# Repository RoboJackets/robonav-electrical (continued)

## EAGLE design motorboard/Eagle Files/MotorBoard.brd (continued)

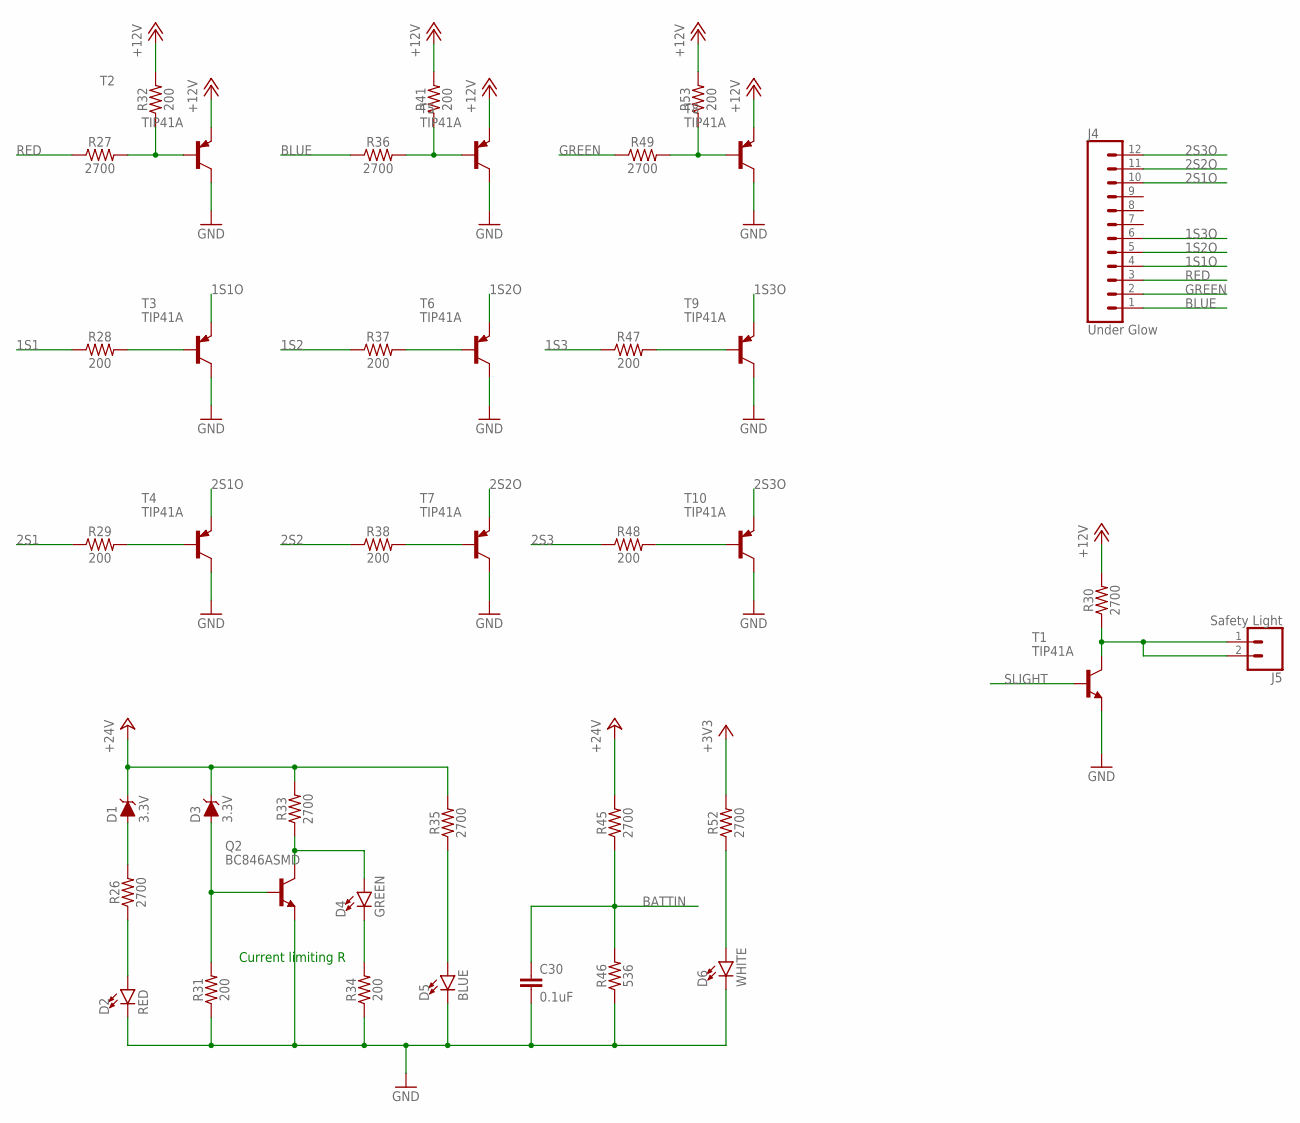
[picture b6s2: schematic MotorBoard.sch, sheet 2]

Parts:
C30: 0.1uF; 0603
D1, D3: 3.3V; SOD-323
D2: RED; LED-0603
D4: GREEN; LED-0603
D5: BLUE; LED-0603
D6: WHITE; LED-0603
J4: Under Glow; 1X12_LOCK_LONGPADS
J5: Safety Light; MOLEX-1X2
Q2: BC846ASMD; SOT23
R26, R27, R30, R33, R35, R36, R45, R49, R52: 2700; 0603
R28, R29, R31, R32, R34, R37, R38, R41, R47, R48, R53: 200; 0603
R46: 536; 0603
T1, T2, T3, T4, T5, T6, T7, T8, T9, T10: TIP41A; TO220V

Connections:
1S1: R28.1; also elsewhere on the board
1S1O: J4.4, T3.3 (E)
1S2: R37.1; also elsewhere on the board
1S2O: J4.5, T6.3 (E)
1S3: R47.1; also elsewhere on the board
1S3O: J4.6, T9.3 (E)
2S1: R29.1; also elsewhere on the board
2S1O: J4.10, T4.3 (E)
2S2: R38.1; also elsewhere on the board
2S2O: J4.11, T7.3 (E)
2S3: R48.1; also elsewhere on the board
2S3O: J4.12, T10.3 (E)
+3V3: R52.2; also elsewhere on the board
+12V: R30.2, R32.2, R41.2, R53.2, T2.3 (E), T5.3 (E), T8.3 (E); also elsewhere on the board
+24V: D1.C, D3.C, R33.2, R35.2, R45.2; also elsewhere on the board
BATTIN: C30.1, R45.1, R46.2; also elsewhere on the board
BLUE: J4.1, R36.1
GND: C30.2, D2.C, D5.C, D6.C, Q2.2 (E), R31.1, R34.1, R46.1, T1.3 (E), T2.2 (C), T3.2 (C), T4.2 (C), T5.2 (C), T6.2 (C), T7.2 (C), T8.2 (C), T9.2 (C), T10.2 (C); also elsewhere on the board
GREEN: J4.2, R49.1
unnamed: J5.1, J5.2, R30.1, T1.2 (C)
unnamed: R27.2, R32.1, T2.1 (B)
unnamed: R36.2, R41.1, T5.1 (B)
unnamed: R49.2, R53.1, T8.1 (B)
unnamed: R47.2, T9.1 (B)
unnamed: R37.2, T6.1 (B)
unnamed: R28.2, T3.1 (B)
unnamed: R29.2, T4.1 (B)
unnamed: R38.2, T7.1 (B)
unnamed: R48.2, T10.1 (B)
unnamed: D1.A, R26.2
unnamed: D2.A, R26.1
unnamed: D4.C, R34.2
unnamed: D3.A, Q2.1 (B), R31.2
unnamed: D5.A, R35.1
unnamed: D4.A, Q2.3 (C), R33.1
unnamed: D6.A, R52.1
RED: J4.3, R27.1
SLIGHT: T1.1 (B); also elsewhere on the board

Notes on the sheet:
Current limiting R

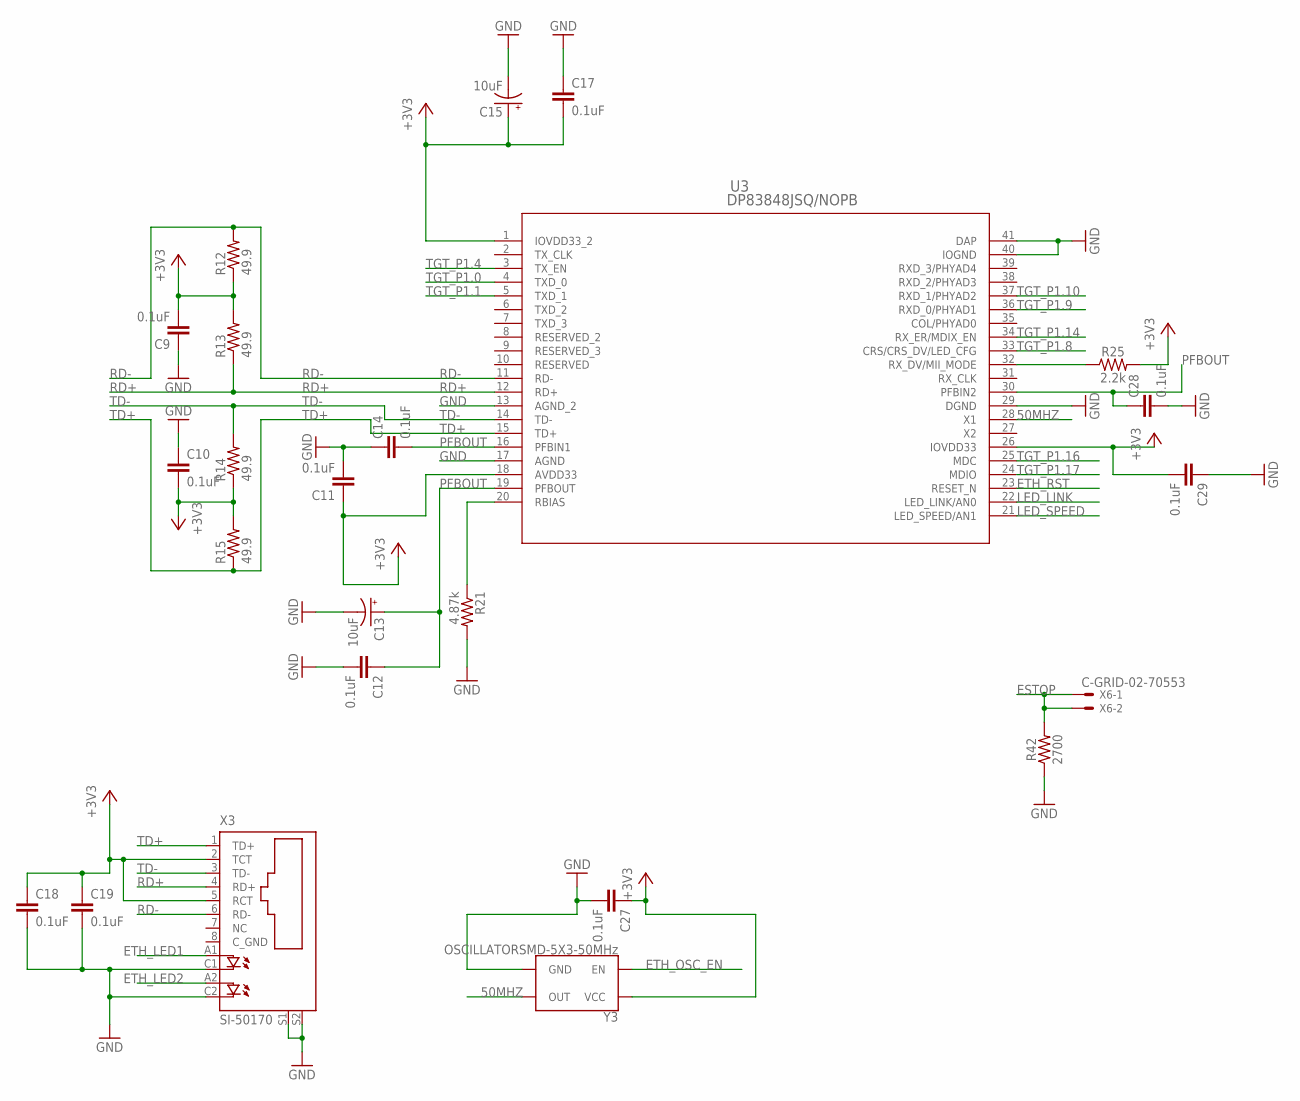
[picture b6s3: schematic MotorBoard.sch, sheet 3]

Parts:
C9, C10, C11, C12, C14, C17, C18, C19, C27, C28, C29: 0.1uF; 0603
C13, C15: 10uF; 0603-POLAR
R12, R13, R14, R15: 49.9; R0603
R21: 4.87k; R0603
R25: 2.2k; 0603
R42: 2700; 0603
U3: DP83848JSQ/NOPB; SQA40B
X3: SI-50170
X6: C-GRID-02-70553; 70553-02
Y3: OSCILLATORSMD-5X3-50MHz; OSCILLATOR-SMD-5X3.2

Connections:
50MHZ: U3.28 (X1), Y3.3 (OUT); also elsewhere on the board
+3V3: C9.2, C10.2, C11.1, C15.+, C17.2, C18.1, C19.1, C27.1, C29.2, R12.1, R13.2, R14.1, R15.2, R25.2, U3.1 (IOVDD33_2), U3.18 (AVDD33), U3.26 (IOVDD33), X3.2 (TCT), X3.5 (RCT), Y3.4 (VCC); also elsewhere on the board
ESTOP: R42.2, X6.1, X6.2; also elsewhere on the board
ETH_LED1: X3.A1 (A); also elsewhere on the board
ETH_LED2: X3.A2 (A1); also elsewhere on the board
ETH_OSC_EN: Y3.1 (EN); also elsewhere on the board
ETH_RST: U3.23 (RESET_N); also elsewhere on the board
GND: C9.1, C10.1, C11.2, C12.2, C13.-, C14.1, C15.-, C17.1, C18.2, C19.2, C27.2, C28.2, C29.1, R21.2, R42.1, U3.13 (AGND_2), U3.17 (AGND), U3.29 (DGND), U3.40 (IOGND), U3.41 (DAP), X3.C1 (C), X3.C2 (C1), X3.S1, X3.S2, Y3.2 (GND); also elsewhere on the board
LED_LINK: U3.22 (LED_LINK/AN0); also elsewhere on the board
LED_SPEED: U3.21 (LED_SPEED/AN1); also elsewhere on the board
unnamed: R21.1, U3.20 (RBIAS)
unnamed: R25.1, U3.32 (RX_DV/MII_MODE)
PFBOUT: C12.1, C13.+, C14.2, C28.1, U3.16 (PFBIN1), U3.19 (PFBOUT), U3.30 (PFBIN2)
RD+: R13.1, U3.12 (RD+), X3.4 (RD+)
RD-: R12.2, U3.11 (RD-), X3.6 (RD-)
TD+: R15.1, U3.15 (TD+), X3.1 (TD+)
TD-: R14.2, U3.14 (TD-), X3.3 (TD-)
TGT_P1.0: U3.4 (TXD_0); also elsewhere on the board
TGT_P1.1: U3.5 (TXD_1); also elsewhere on the board
TGT_P1.4: U3.3 (TX_EN); also elsewhere on the board
TGT_P1.8: U3.33 (CRS/CRS_DV/LED_CFG); also elsewhere on the board
TGT_P1.9: U3.36 (RXD_0/PHYAD1); also elsewhere on the board
TGT_P1.10: U3.37 (RXD_1/PHYAD2); also elsewhere on the board
TGT_P1.14: U3.34 (RX_ER/MDIX_EN); also elsewhere on the board
TGT_P1.16: U3.25 (MDC); also elsewhere on the board
TGT_P1.17: U3.24 (MDIO); also elsewhere on the board

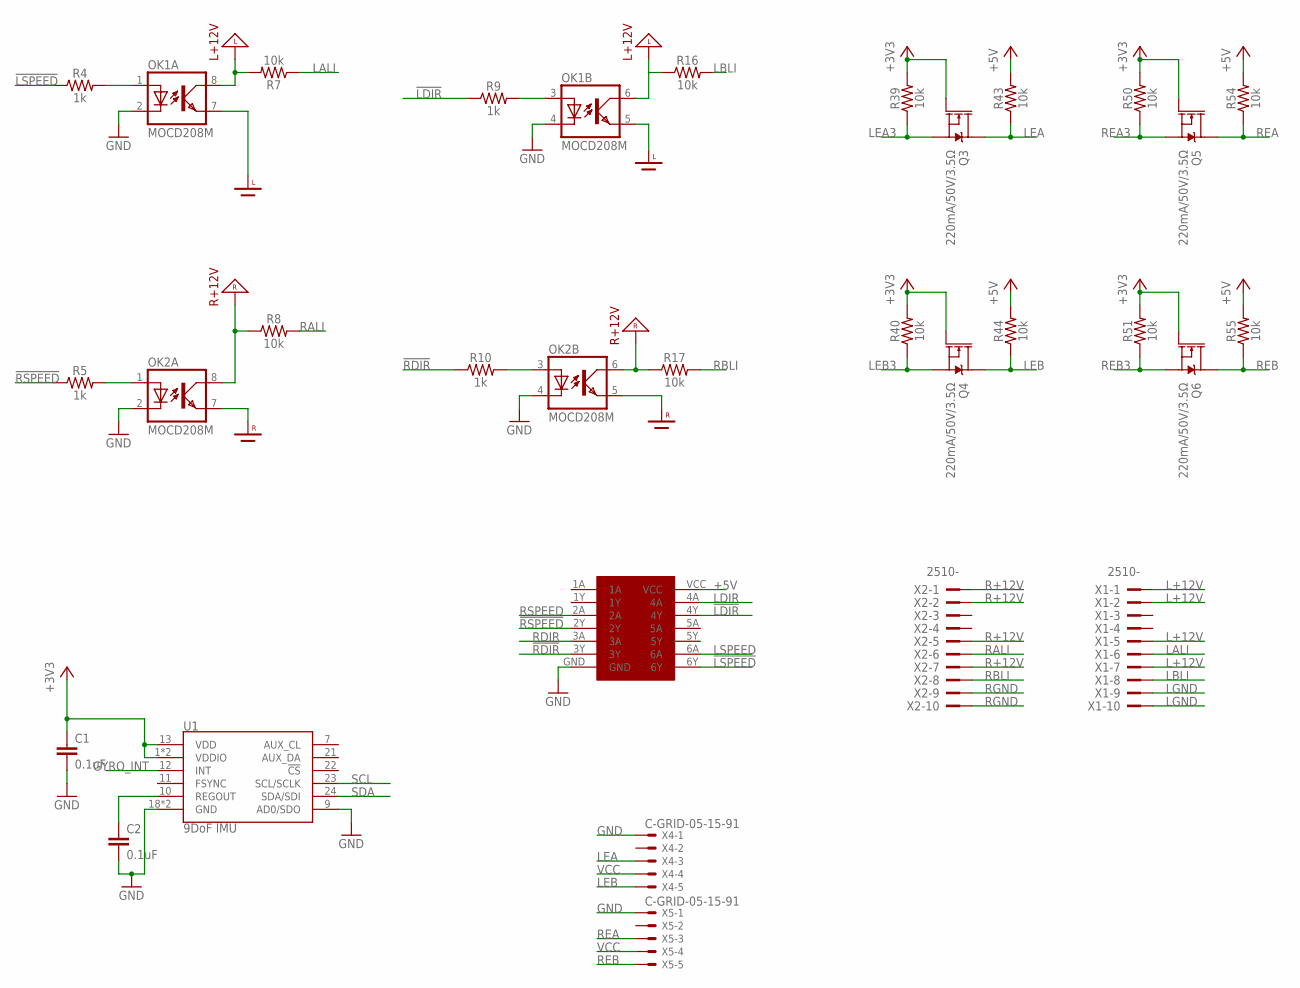
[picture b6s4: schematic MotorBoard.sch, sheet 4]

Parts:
C1, C2: 0.1uF; 0603
OK1, OK2: MOCD208M; SOIC08-FAIRCHILD
Q3, Q4, Q5, Q6: 220mA/50V/3.5Ω; SOT23-3
R4, R5, R9, R10: 1k; 0603
R7, R8, R16, R17, R39, R40, R43, R44, R50, R51, R54, R55: 10k; 0603
U1: 9DoF IMU; QFN24-3X3
U$14: ICHEXINV; 74HC14
X1, X2: 2510-; PAK100/2500-10
X4, X5: C-GRID-05-15-91; 15-91-05

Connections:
!LDIR!: R9.1, U$14.4Y
!LSPEED!: R4.1, U$14.6Y
!RDIR!: R10.1, U$14.3Y
!RSPEED!: R5.1, U$14.2Y
+3V3: C1.1, Q3.1 (G), Q4.1 (G), Q5.1 (G), Q6.1 (G), R39.2, R40.2, R50.2, R51.2, U1.1 (VDDIO), U1.8 (VDDIO), U1.13 (VDD); also elsewhere on the board
+5V: R43.2, R44.2, R54.2, R55.2, U$14.VCC; also elsewhere on the board
GND: C1.2, C2.2, OK1.2 (C), OK1.4 (C), OK2.2 (C), OK2.4 (C), U1.9 (AD0/SDO), U1.18 (GND), U1.20 (GND), U$14.GND, X4.1, X5.1; also elsewhere on the board
GYRO_INT: U1.12 (INT); also elsewhere on the board
L+12V: OK1.6 (COL), OK1.8 (COL), R7.2, R16.1, X1.1, X1.2, X1.5, X1.7
LALI: R7.1, X1.6
LBLI: R16.2, X1.8
LDIR: U$14.4A; also elsewhere on the board
LEA: Q3.3 (D), R43.1, X4.3
LEA3: Q3.2 (S), R39.1; also elsewhere on the board
LEB: Q4.3 (D), R44.1, X4.5
LEB3: Q4.2 (S), R40.1; also elsewhere on the board
LGND: OK1.5 (EMIT), OK1.7 (EMIT), X1.9, X1.10
LSPEED: U$14.6A; also elsewhere on the board
unnamed: OK1.1 (A), R4.2
unnamed: OK2.1 (A), R5.2
unnamed: OK2.3 (A), R10.2
unnamed: OK1.3 (A), R9.2
unnamed: C2.1, U1.10 (REGOUT)
R+12V: OK2.6 (COL), OK2.8 (COL), R8.1, R17.1, X2.1, X2.2, X2.5, X2.7
RALI: R8.2, X2.6
RBLI: R17.2, X2.8
RDIR: U$14.3A; also elsewhere on the board
REA: Q5.3 (D), R54.1, X5.3
REA3: Q5.2 (S), R50.1; also elsewhere on the board
REB: Q6.3 (D), R55.1, X5.5
REB3: Q6.2 (S), R51.1; also elsewhere on the board
RGND: OK2.5 (EMIT), OK2.7 (EMIT), X2.9, X2.10
RSPEED: U$14.2A; also elsewhere on the board
SCL: U1.23 (SCL/SCLK); also elsewhere on the board
SDA: U1.24 (SDA/SDI); also elsewhere on the board
VCC: X4.4, X5.4

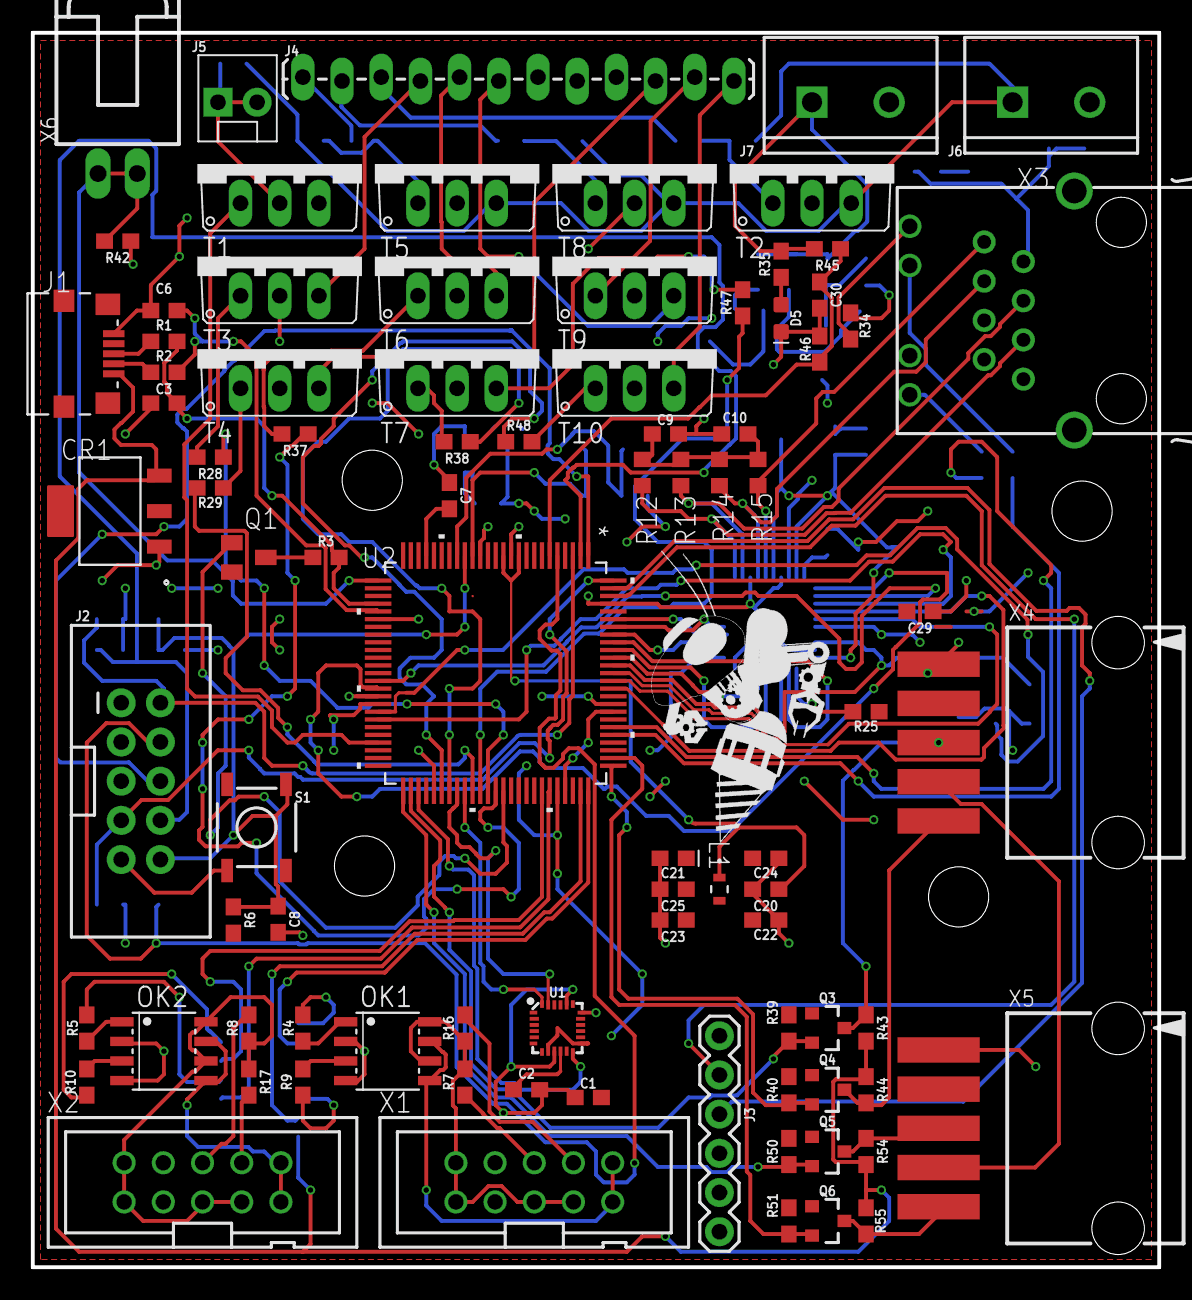
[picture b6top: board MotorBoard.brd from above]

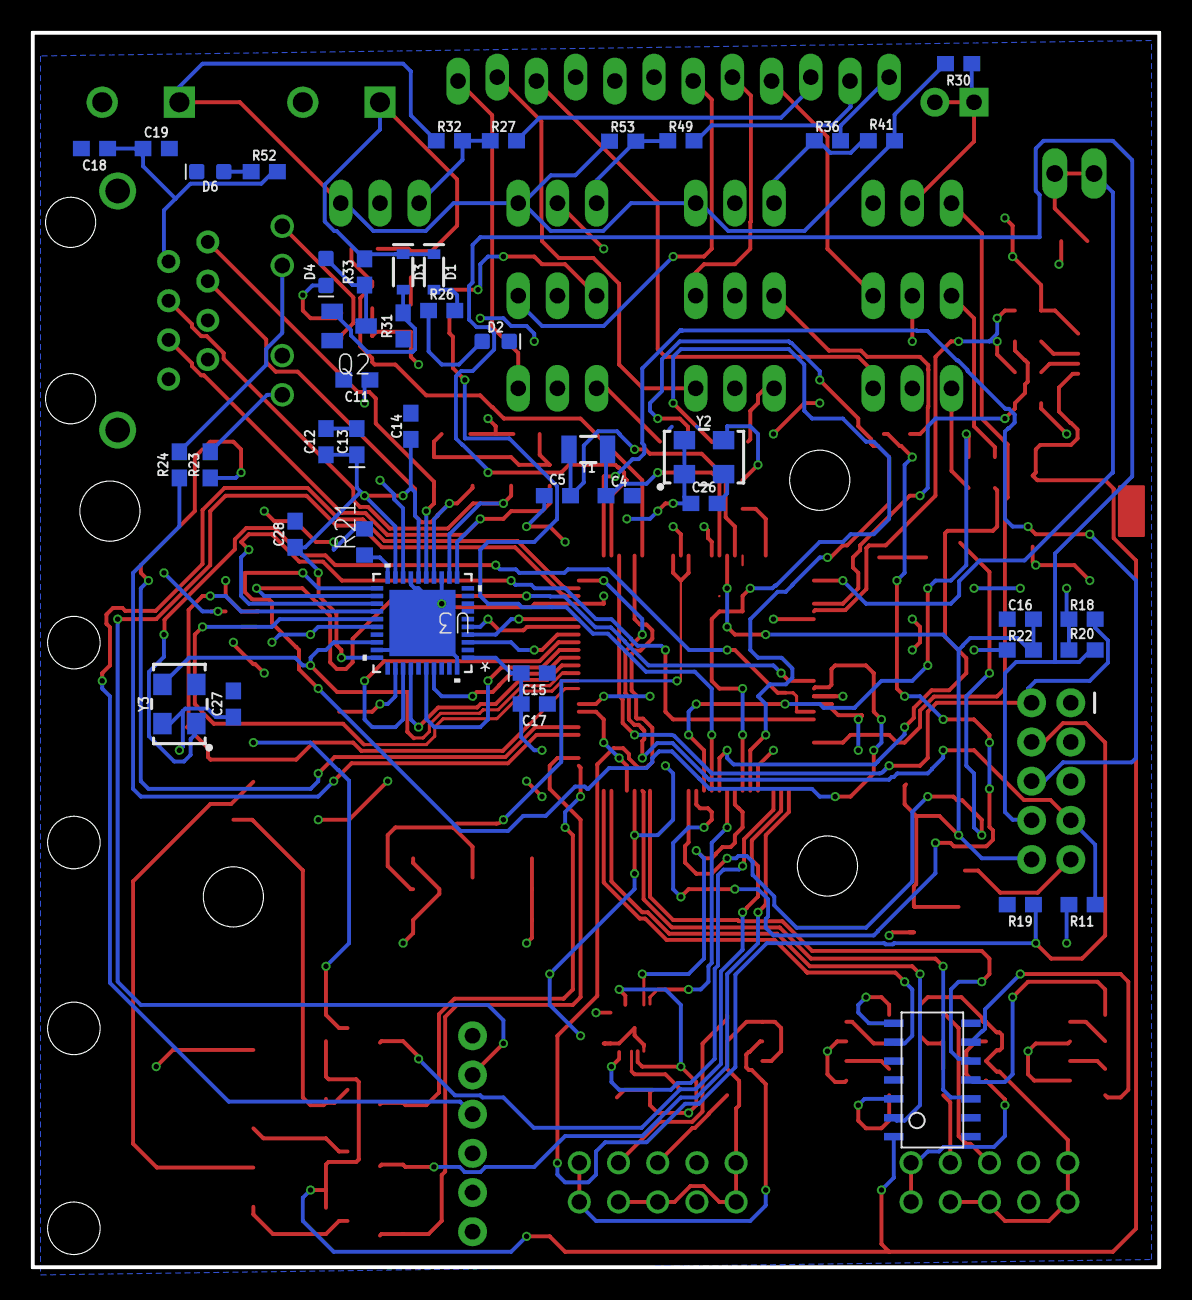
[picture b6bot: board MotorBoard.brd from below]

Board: 2 copper layers, 73.0 x 80.0 mm, 137 parts (44 on the bottom side), 117 nets.

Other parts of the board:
U$3, U$4, U$5, U$6: STANDOFF-HOLE
U$13: ROBOBUZZ_1.0X

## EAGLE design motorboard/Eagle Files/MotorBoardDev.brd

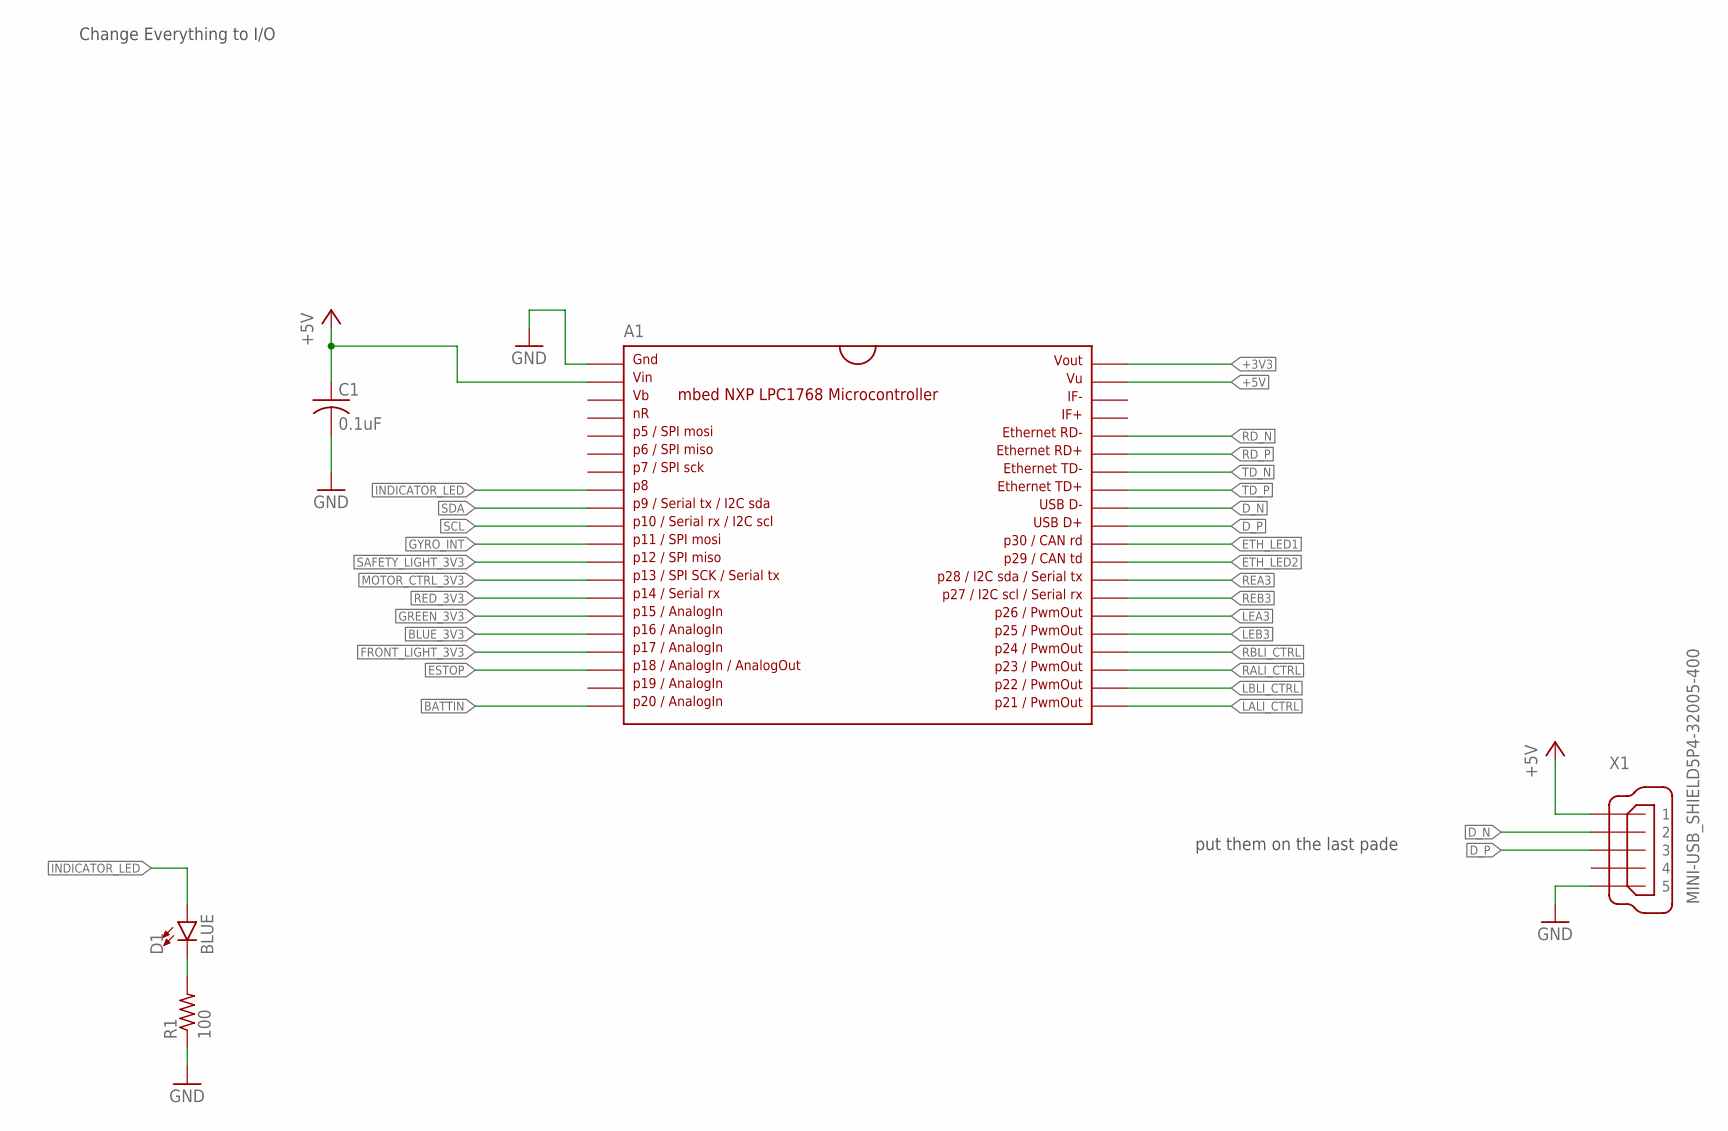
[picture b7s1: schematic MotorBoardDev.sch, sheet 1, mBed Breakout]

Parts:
A1: MBED1768; SPARKFUN-BOARDS_DIL40_0.9
C1: 0.1uF; C0603
D1: BLUE; LED-0603
R1: 100; R0603
X1: MINI-USB_SHIELD5P4-32005-400; 32005-400

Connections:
+3V3: A1.40; also elsewhere on the board
+5V: A1.2, A1.39, C1.1, X1.1; also elsewhere on the board
BATTIN: A1.20; also elsewhere on the board
BLUE_3V3: A1.16; also elsewhere on the board
D_N: A1.32, X1.2
D_P: A1.31, X1.3
ESTOP: A1.18; also elsewhere on the board
ETH_LED1: A1.30; also elsewhere on the board
ETH_LED2: A1.29; also elsewhere on the board
FRONT_LIGHT_3V3: A1.17; also elsewhere on the board
GND: A1.1, C1.2, R1.1, X1.5; also elsewhere on the board
GREEN_3V3: A1.15; also elsewhere on the board
GYRO_INT: A1.11; also elsewhere on the board
INDICATOR_LED: A1.8, D1.A
INDI_LED_R: D1.C, R1.2
LALI_CTRL: A1.21; also elsewhere on the board
LBLI_CTRL: A1.22; also elsewhere on the board
LEA3: A1.26; also elsewhere on the board
LEB3: A1.25; also elsewhere on the board
MOTOR_CTRL_3V3: A1.13; also elsewhere on the board
RALI_CTRL: A1.23; also elsewhere on the board
RBLI_CTRL: A1.24; also elsewhere on the board
RD_N: A1.36; also elsewhere on the board
RD_P: A1.35; also elsewhere on the board
REA3: A1.28; also elsewhere on the board
REB3: A1.27; also elsewhere on the board
RED_3V3: A1.14; also elsewhere on the board
SAFETY_LIGHT_3V3: A1.12; also elsewhere on the board
SCL: A1.10; also elsewhere on the board
SDA: A1.9; also elsewhere on the board
TD_N: A1.34; also elsewhere on the board
TD_P: A1.33; also elsewhere on the board

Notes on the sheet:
Change Everything to I/O
put them on the last pade

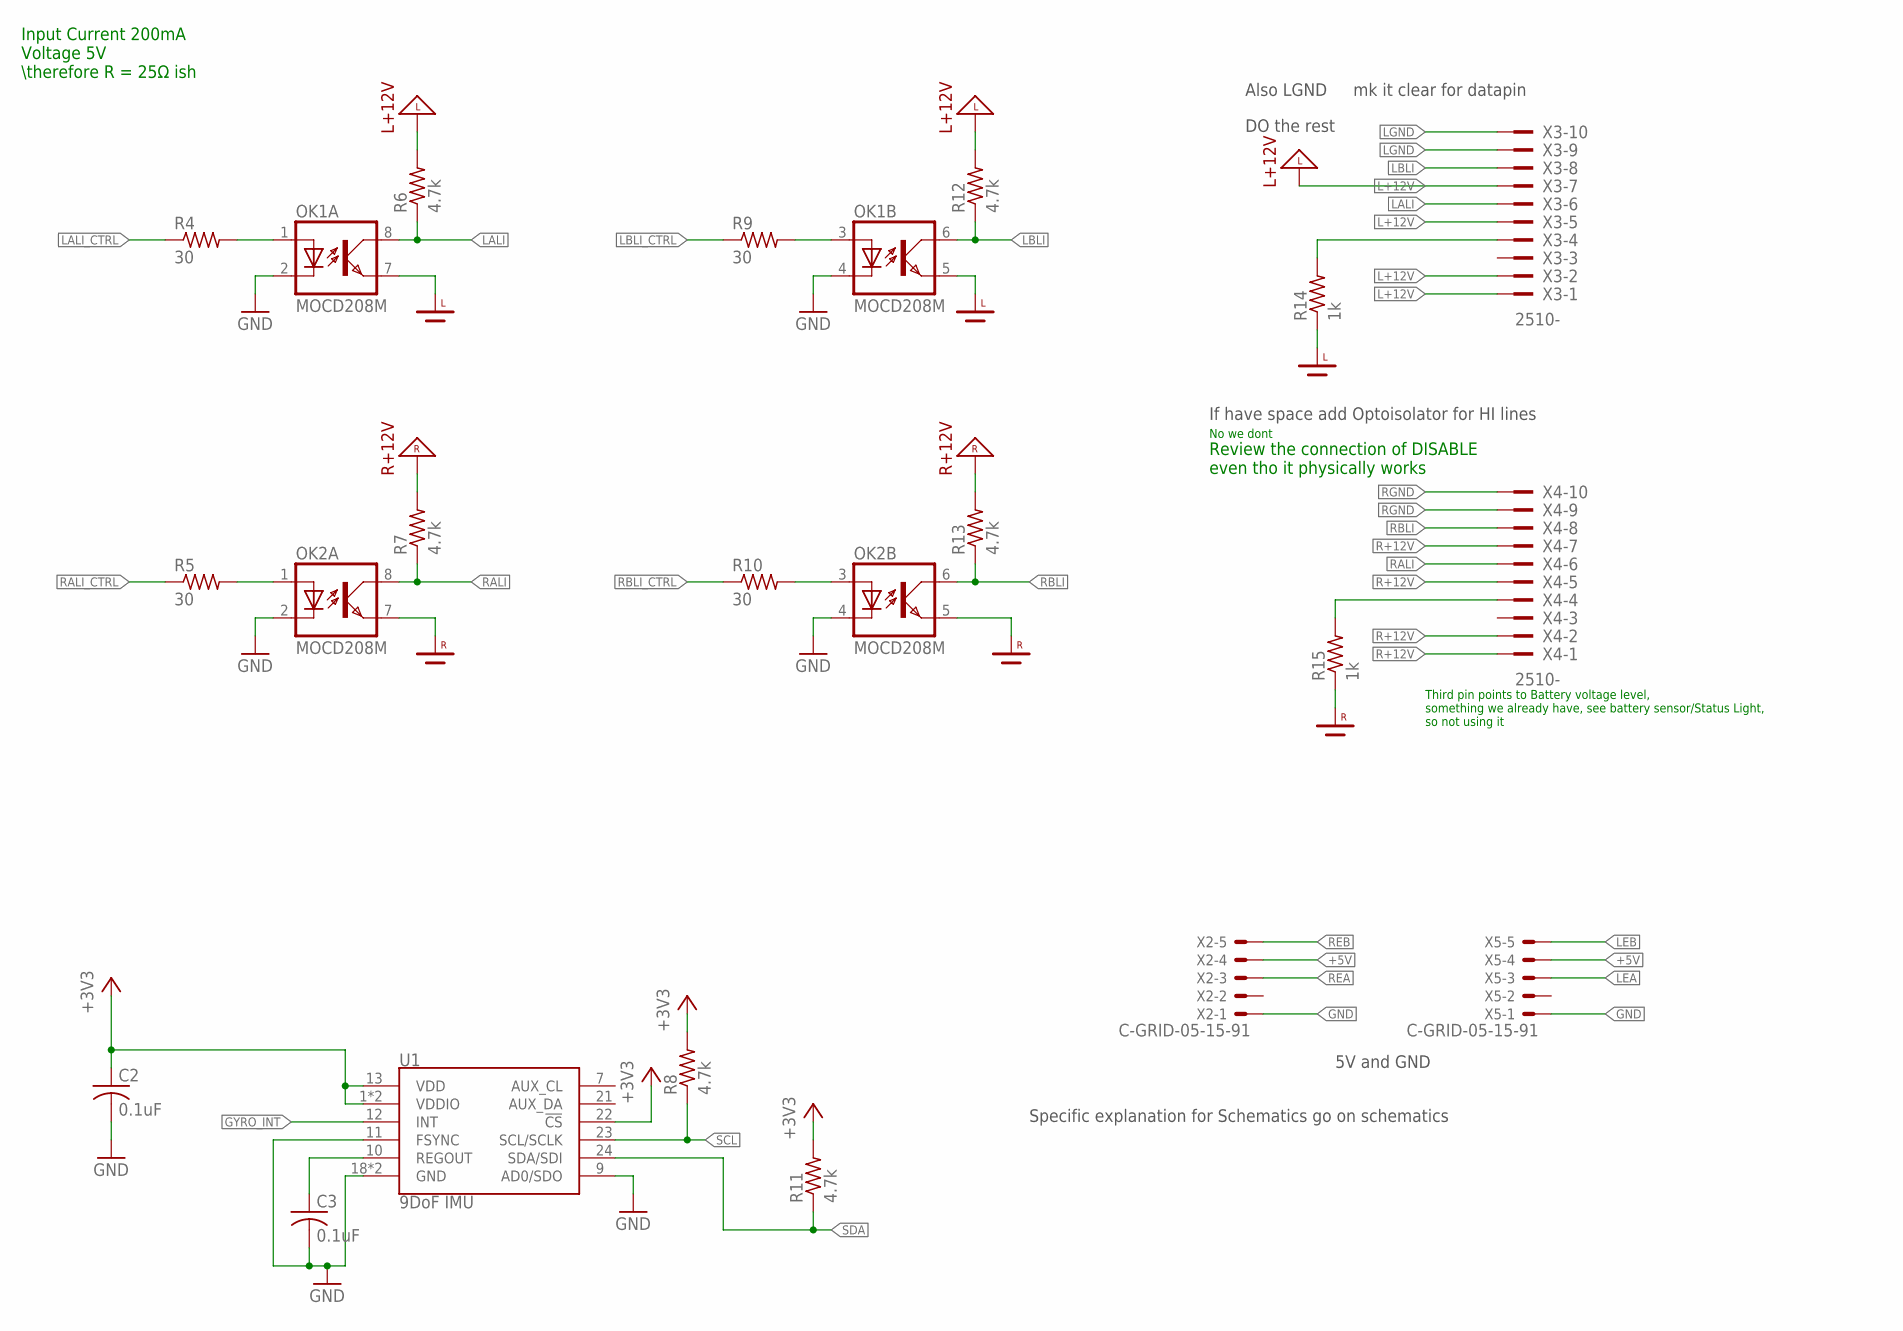
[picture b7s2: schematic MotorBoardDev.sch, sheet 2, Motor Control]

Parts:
C2, C3: 0.1uF; C0603
OK1, OK2: MOCD208M; SOIC08-FAIRCHILD
R4, R5, R9, R10: 30; R0603
R6, R7, R8, R11, R12, R13: 4.7k; R0603
R14, R15: 1k; R0603
U1: 9DoF IMU; QFN24-3X3
X2, X5: C-GRID-05-15-91; 15-91-05
X3, X4: 2510-; PAK100/2500-10

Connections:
+3V3: C2.1, R8.2, R11.2, U1.1 (VDDIO), U1.8 (VDDIO), U1.13 (VDD), U1.22 (!CS); also elsewhere on the board
+5V: X2.4, X5.4; also elsewhere on the board
GND: C2.2, C3.2, OK1.2 (C), OK1.4 (C), OK2.2 (C), OK2.4 (C), U1.9 (AD0/SDO), U1.11 (FSYNC), U1.18 (GND), U1.20 (GND), X2.1, X5.1; also elsewhere on the board
GYRO_INT: U1.12 (INT); also elsewhere on the board
L+12V: R6.2, R12.2, X3.1, X3.2, X3.5, X3.7
LALI: OK1.8 (COL), R6.1, X3.6
LALI_CTRL: R4.1; also elsewhere on the board
LBLI: OK1.6 (COL), R12.1, X3.8
LBLI_CTRL: R9.1; also elsewhere on the board
LDISABLE: R14.2, X3.4
LEA: X5.3; also elsewhere on the board
LEB: X5.5; also elsewhere on the board
LGND: OK1.5 (EMIT), OK1.7 (EMIT), R14.1, X3.9, X3.10
R+12V: R7.2, R13.2, X4.1, X4.2, X4.5, X4.7
RALI: OK2.8 (COL), R7.1, X4.6
RALI_CTRL: R5.1; also elsewhere on the board
RBLI: OK2.6 (COL), R13.1, X4.8
RBLI_CTRL: R10.1; also elsewhere on the board
RDISABLE: R15.2, X4.4
REA: X2.3; also elsewhere on the board
REB: X2.5; also elsewhere on the board
REGOUT_C: C3.1, U1.10 (REGOUT)
RGND: OK2.5 (EMIT), OK2.7 (EMIT), R15.1, X4.9, X4.10
R_OK3A: OK1.1 (A), R4.2
R_OK3B: OK1.3 (A), R9.2
R_OK4A: OK2.1 (A), R5.2
R_OK4B: OK2.3 (A), R10.2
SCL: R8.1, U1.23 (SCL/SCLK); also elsewhere on the board
SDA: R11.1, U1.24 (SDA/SDI); also elsewhere on the board

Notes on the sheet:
If have space add Optoisolator for HI lines
Input Current 200mA Voltage 5V \therefore R = 25Ω ish
Third pin points to Battery voltage level, something we already have, see battery sensor/Status Light, so not using it
No we dont
Review the connection of DISABLE even tho it physically works
DO the rest
Also LGND
mk it clear for datapin
5V and GND
Specific explanation for Schematics go on schematics

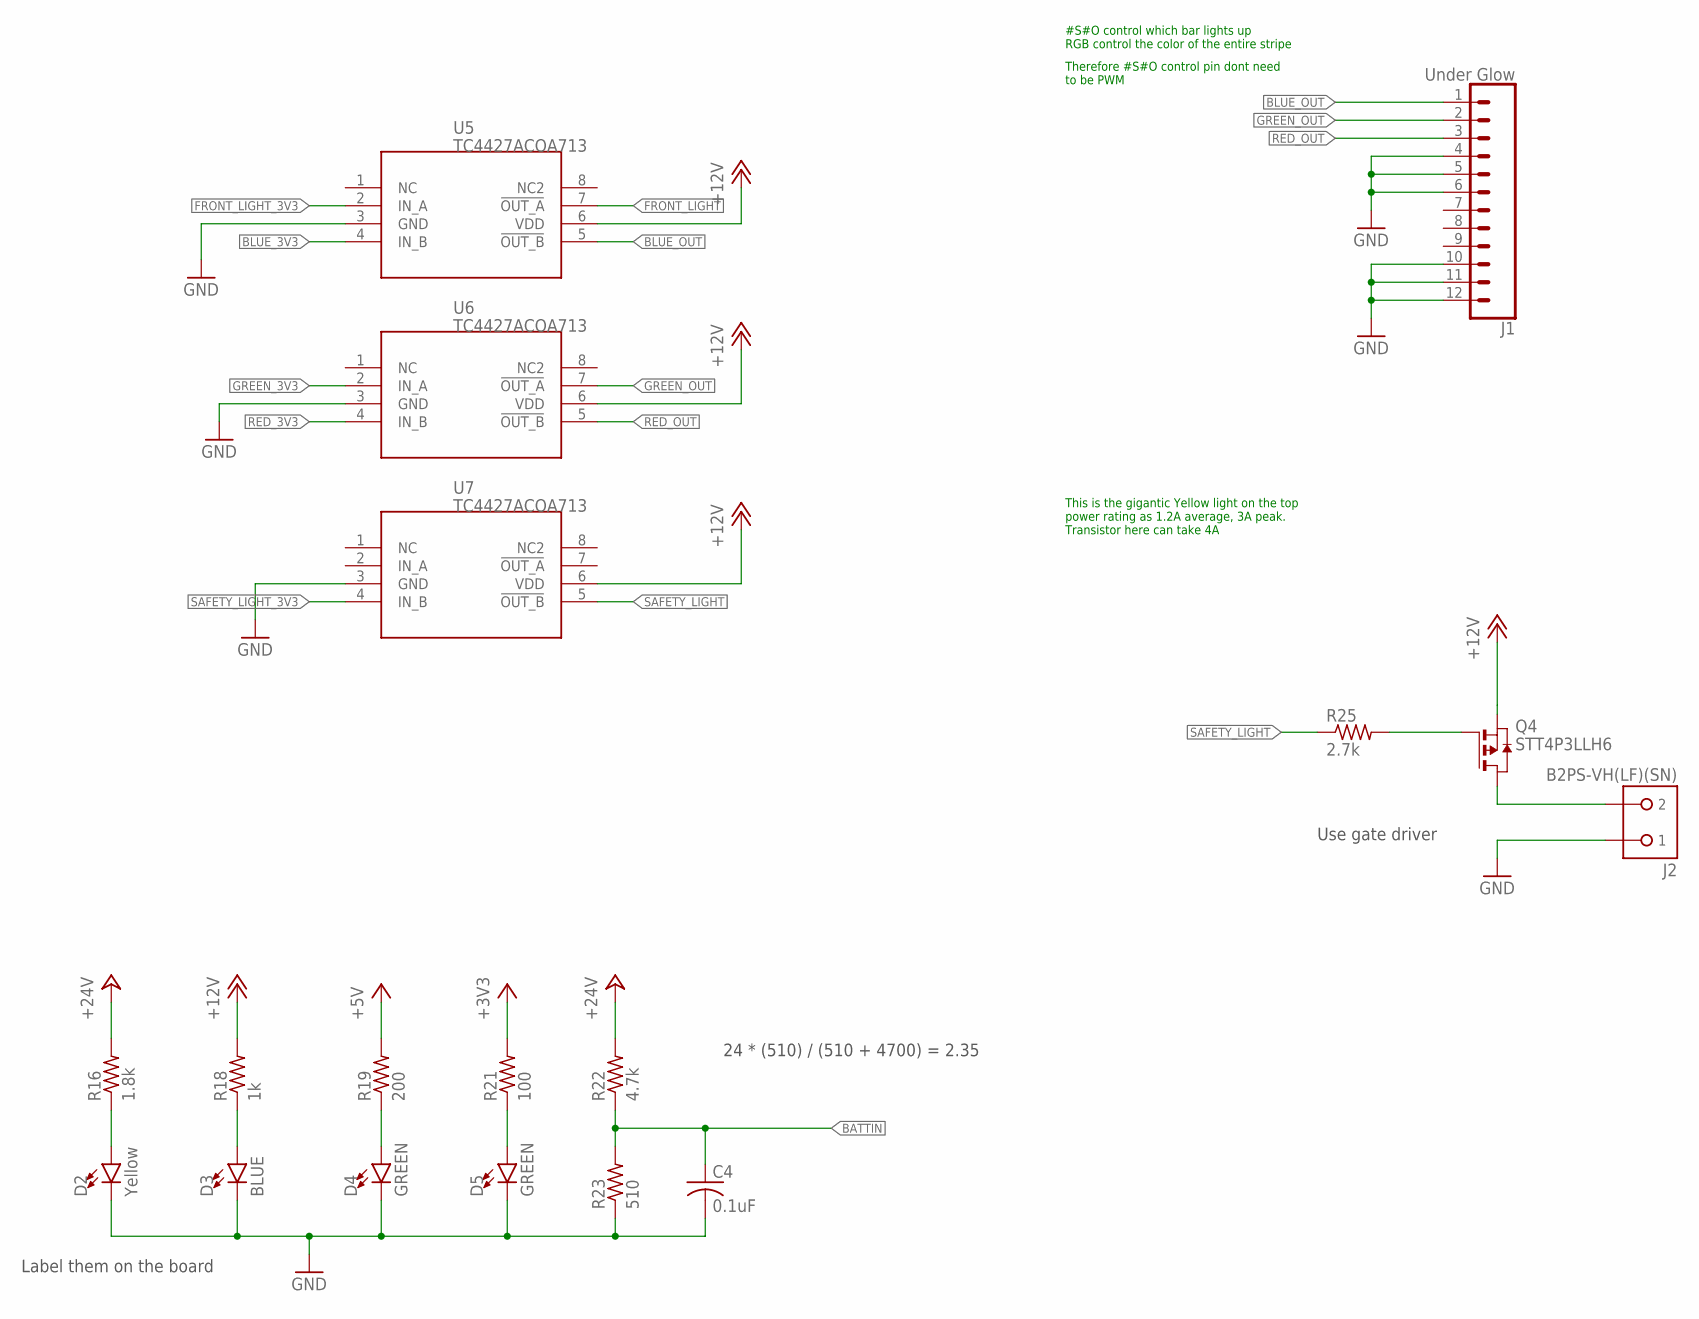
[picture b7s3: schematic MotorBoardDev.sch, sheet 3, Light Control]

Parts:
C4: 0.1uF; C0603
D2: Yellow; LED-0603
D3: BLUE; LED-0603
D4, D5: GREEN; LED-0603
J1: Under Glow; 1X12_LOCK_LONGPADS
J2: B2PS-VH(LF)(SN); B2PS-CENTERED
Q4: STT4P3LLH6; SOT23-6
R16: 1.8k; R0603
R18: 1k; R0603
R19: 200; R0603
R21: 100; R0603
R22: 4.7k; R0603
R23: 510; R0603
R25: 2.7k; R0603
U5, U6, U7: TC4427ACOA713; SOIC-8

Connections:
3V3_LED_R: D5.A, R21.1
5V_LED_R: D4.A, R19.1
12V_LED_R: D3.A, R18.1
24V_LED_R: D2.A, R16.1
+3V3: R21.2; also elsewhere on the board
+5V: R19.2; also elsewhere on the board
+12V: Q4.4 (S), R18.2, U5.6 (VDD), U6.6 (VDD), U7.6 (VDD); also elsewhere on the board
+24V: R16.2, R22.2; also elsewhere on the board
BATTIN: C4.1, R22.1, R23.2; also elsewhere on the board
BLUE_3V3: U5.4 (IN_B); also elsewhere on the board
BLUE_OUT: J1.1, U5.5 (!OUT_B)
FRONT_LIGHT: U5.7 (!OUT_A); also elsewhere on the board
FRONT_LIGHT_3V3: U5.2 (IN_A); also elsewhere on the board
GND: C4.2, D2.C, D3.C, D4.C, D5.C, J1.4, J1.5, J1.6, J1.10, J1.11, J1.12, J2.1, R23.1, U5.3 (GND), U6.3 (GND), U7.3 (GND); also elsewhere on the board
GREEN_3V3: U6.2 (IN_A); also elsewhere on the board
GREEN_OUT: J1.2, U6.7 (!OUT_A)
RED_3V3: U6.4 (IN_B); also elsewhere on the board
RED_OUT: J1.3, U6.5 (!OUT_B)
SAFETY_HRD: J2.2, Q4.1 (D), Q4.2 (D), Q4.5 (D), Q4.6 (D)
SAFETY_LIGHT: R25.1, U7.5 (!OUT_B)
SAFETY_LIGHT_3V3: U7.4 (IN_B); also elsewhere on the board
SAFETY_R: Q4.3 (G), R25.2

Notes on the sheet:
Label them on the board
#S#O control which bar lights up RGB control the color of the entire stripe
Therefore #S#O control pin dont need to be PWM
This is the gigantic Yellow light on the top power rating as 1.2A average, 3A peak. Transistor here can take 4A
24 * (510) / (510 + 4700) = 2.35
Use gate driver
